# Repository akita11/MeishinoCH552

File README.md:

# MeishinoCH552

つくった基板を名刺代わりに！

基板の表や裏の空いているところに、自分の名前などをシルクで入れれば、オリジナル基板のできあがり。
あとは製造発注して、名刺代わりに配りましょう。

## マイコンボードとしての使い方

基板製造時に部品実装(PCBA)もいっしょに注文すれば、ArduinoIDEでプログラムを書けるマイコンボードとしても使えます。もちろん自分で部品をはんだ付けしてもOK。
（[CH552duino](https://github.com/akita11/CH552duino)と同じ構成ですので、これの使い方を参照してください。[使い方を含めた解説書](https://techbookfest.org/product/5803512929714176)もあります。）

PCにつなぐUSB端子は、以下の3つのいずれかを使えます。

- 基板の一部にあるUSB端子を直接PCへ（USB端子の周りの板を切り取って使います。（※板厚2.0mm。それより薄い場合は厚紙などをはさむ）
- 基板上部にあるUSB Type-C端子にUSB Type-Cケーブルで接続（※板厚0.6mm）
- 基板上にUSB Type-Cコネクタを実装し、USB Type-Cケーブルで接続

## オリジナル基板のつくりから

プリント基板設計CADの[KiCAD](https://www.kicad.org/)で名前などを記入し、オリジナル基板をつくることができます。
文字だけでなく、画像を入れることもできます。名前などが書かれた画像データを用意します。例してPowerPointファイル(namecard.pptx)を用意してあります。この枠内をスクリーンショットで保存するのが簡単でいいでしょう。

画像データはKiCADの"Bitmap Converter"で、KiCADで使える部品（フットプリント）に変換してから、基板に読み込んで配置すればOKです。例として、名前などを入れたもの（MeishinoCH552_sample.kicad_pcb）を用意してありますので参考にしてください。

# 基板の製造

製造用ガーバーデータ（MeishinoCH552_gerber.zip：ただし名前などは何も入っていない）を使うか、[KiCAD](https://www.kicad.org/)で設計したものから製造用ガーバーデータを出力します。

基板製造は、[JLCPCB](https://jlcpcb.com/)などのオンラインサービスを使うと便利です。

基板の色（レジスト）は自由です。基板上部のUSB Type-C端子を使うためには、板厚は0.6mmとしてください（これを使わない場合は板厚は自由）。

# 部品の調達と実装

部品表（MeishinoCH552_BOM_JLCSMT.xlsx）の部品を[LCSC](https://lcsc.com/)などで購入し、手ハンダなどの方法で部品を実装します。あるいは、この部品表を部品位置ファイル（MeishinoCH552_CPL_JLCSMT.xlsx）とともに[JLCPCB](https://jlcpcb.com/)に注文すれば、部品実装が済んだ状態のものを得ることもできます。

※実際にPCBAを発注する際は、BOMとCPLの内容をよく確認してください。指定している部品が在庫切れの場合や、部品の実装位置・向きが実際とズレている場合があります（これは部品の0度の向きの定義が明確ではないことから生じる不確実性です）ので、ビューア等でよく確認をしてください。

なおUSB Type-Cコネクタを実装せずに、基板パターンを活用したUSB Type-CコネクタにUSBケーブルを接続して使用することにすれば、全体の厚さを2mm程度にすることができます。（ただし何回も抜き差しするとコネクタ部の基板パターンが摩耗により劣化します）

# Author

Junichi Akita (@akita11, akita@ifdl.jp)

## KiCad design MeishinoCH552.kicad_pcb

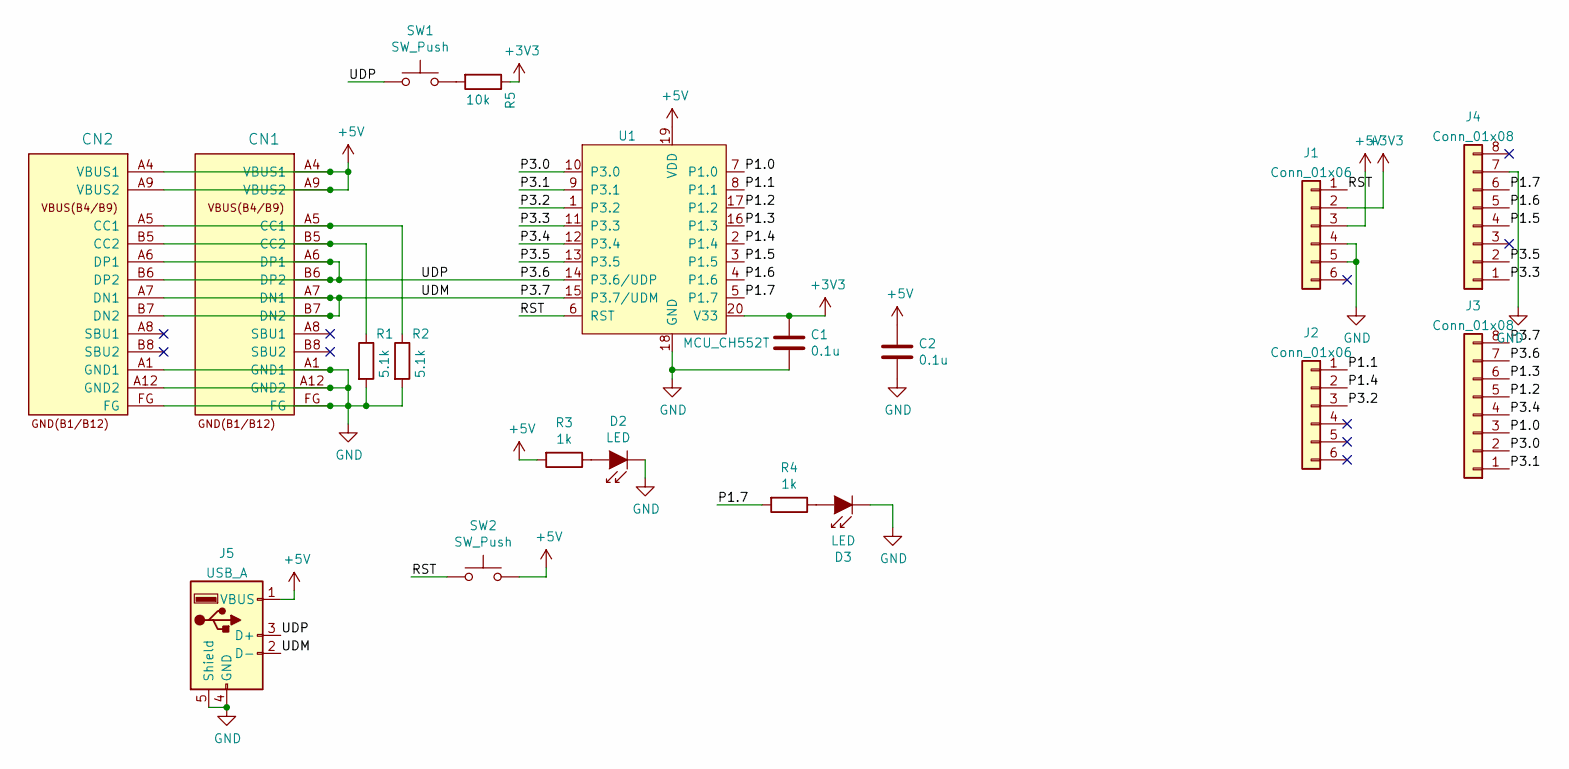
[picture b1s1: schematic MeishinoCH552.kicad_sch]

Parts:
C1, C2: 0.1u; C_0603_1608Metric
CN1: CON_USB-C-16; USB-C_16P_TH
CN2: CON_USB-C-16; USB-C_PCBPLUG
D2, D3: LED; LED_0603_1608Metric
J1, J2: Conn_01x06; PinSocket_1x06_P2.54mm_Vertical
J3, J4: Conn_01x08; PinSocket_1x08_P2.54mm_Vertical
J5: USB_A; USB-A-PCB
R1, R2: 5.1k; R_0603_1608Metric
R3, R4: 1k; R_0603_1608Metric
R5: 10k; R_0603_1608Metric
SW1, SW2: SW_Push; SW_Push_SPST_NO_Alps_SKRK
U1: MCU_CH552T; TSSOP-20_4.4x6.5mm_P0.65mm

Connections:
+3V3: C1.1, J1.2, R5.1, U1.20 (V33)
+5V: C2.1, CN1.A4 (VBUS1), CN1.A9 (VBUS2), CN2.A4 (VBUS1), CN2.A9 (VBUS2), J1.3, J5.1 (VBUS), R3.2, SW2.2, U1.19 (VDD)
/P1.0: J3.3, U1.7 (P1.0)
/P1.1: J2.1, U1.8 (P1.1)
/P1.2: J3.5, U1.17 (P1.2)
/P1.3: J3.6, U1.16 (P1.3)
/P1.4: J2.2, U1.2 (P1.4)
/P1.5: J4.4, U1.3 (P1.5)
/P1.6: J4.5, U1.4 (P1.6)
/P1.7: J4.6, R4.2, U1.5 (P1.7)
/P3.0: J3.2, U1.10 (P3.0)
/P3.1: J3.1, U1.9 (P3.1)
/P3.2: J2.3, U1.1 (P3.2)
/P3.3: J4.1, U1.11 (P3.3)
/P3.4: J3.4, U1.12 (P3.4)
/P3.5: J4.2, U1.13 (P3.5)
/P3.6: CN1.A6 (DP1), CN1.B6 (DP2), CN2.A6 (DP1), CN2.B6 (DP2), J3.7, J5.3 (D+), SW1.1, U1.14 (P3.6/UDP)
/P3.7: CN1.A7 (DN1), CN1.B7 (DN2), CN2.A7 (DN1), CN2.B7 (DN2), J3.8, J5.2 (D-), U1.15 (P3.7/UDM)
/RST: J1.1, SW2.1, U1.6 (RST)
GND: C1.2, C2.2, CN1.A1 (GND1), CN1.A12 (GND2), CN1.FG, CN2.A1 (GND1), CN2.A12 (GND2), CN2.FG, D2.1 (K), D3.1 (K), J1.4, J1.5, J4.7, J5.4 (GND), J5.5 (Shield), R1.2, R2.2, U1.18 (GND)
unnamed: CN1.A5 (CC1), CN2.A5 (CC1), R2.1
unnamed: CN1.B5 (CC2), CN2.B5 (CC2), R1.1
unnamed: D2.2 (A), R3.1
unnamed: D3.2 (A), R4.1
unnamed: R5.2, SW1.2

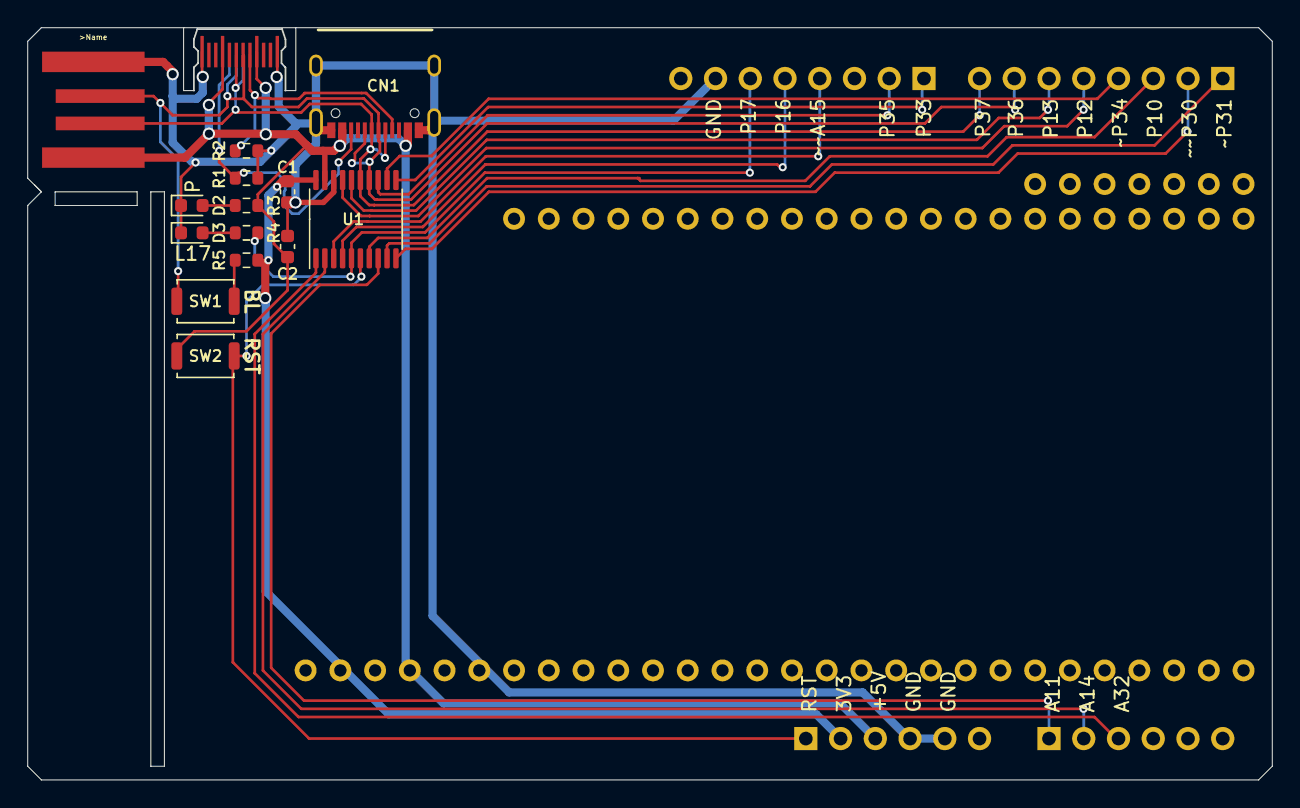
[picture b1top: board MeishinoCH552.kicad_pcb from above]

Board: 2 copper layers, 91.0 x 55.0 mm, 19 parts (0 on the bottom side), 25 nets.

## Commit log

2022-07-03 BOM bug fix
2022-07-03 add PCB photo
2022-07-03 fix photo URL
2022-07-03 Fix coordinate and rotation of CN1 and U1 in the CPL file
2022-07-03 PCBA発注時の注意を追加
2022-07-06 フリー配線エリアのパッドをレジストなしに
